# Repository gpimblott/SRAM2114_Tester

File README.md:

# 2114 SRAM Tester

Tester for 2114 SRAM chips using an Arduino Nano. The code can be loaded into the standard Arduino IDE for uploading/editing.

2114 SRAM chips are used in the ZX81, they are 4096 bit chips arranged in 1024 rows of 4 bits.  This code uses a Arduino Nano to perform various tests on a 2114 chip to check that it is working.

The prototype wiring (v01) is outlined in the table below

Port | Arduino  |  2114
-----|----------|--------
PC0  |A0        |IO1
PC1  |A1        |IO2
PC2  |A2        |IO3
PC3  |A3        |IO4
PC4  |A4        |Green LED
PC5  |A5        |Red LED
PC6  |A6        |Switch
PD0  |0         |Serial (Debug) - leave empty for USB
PD1  |1         |Serial (Debug) - leave empty for USB
PD2  |2         |/CS (Chip Select)
PD3  |3         |/WE (Write Enabled)
PD4  |4         |A0
PD5  |5         |A1
PD6  |6         |A2
PD7  |7         |A3
PB0  |8         |A4
PB1  |9         |A5
PB2  |10        |A6
PB3  |11        |A7
PB4  |12        |A8
PB5  |13        |A9

The project is currently is currently at the prototype stage but I am working on a PCB design which should hopefully be available soon.

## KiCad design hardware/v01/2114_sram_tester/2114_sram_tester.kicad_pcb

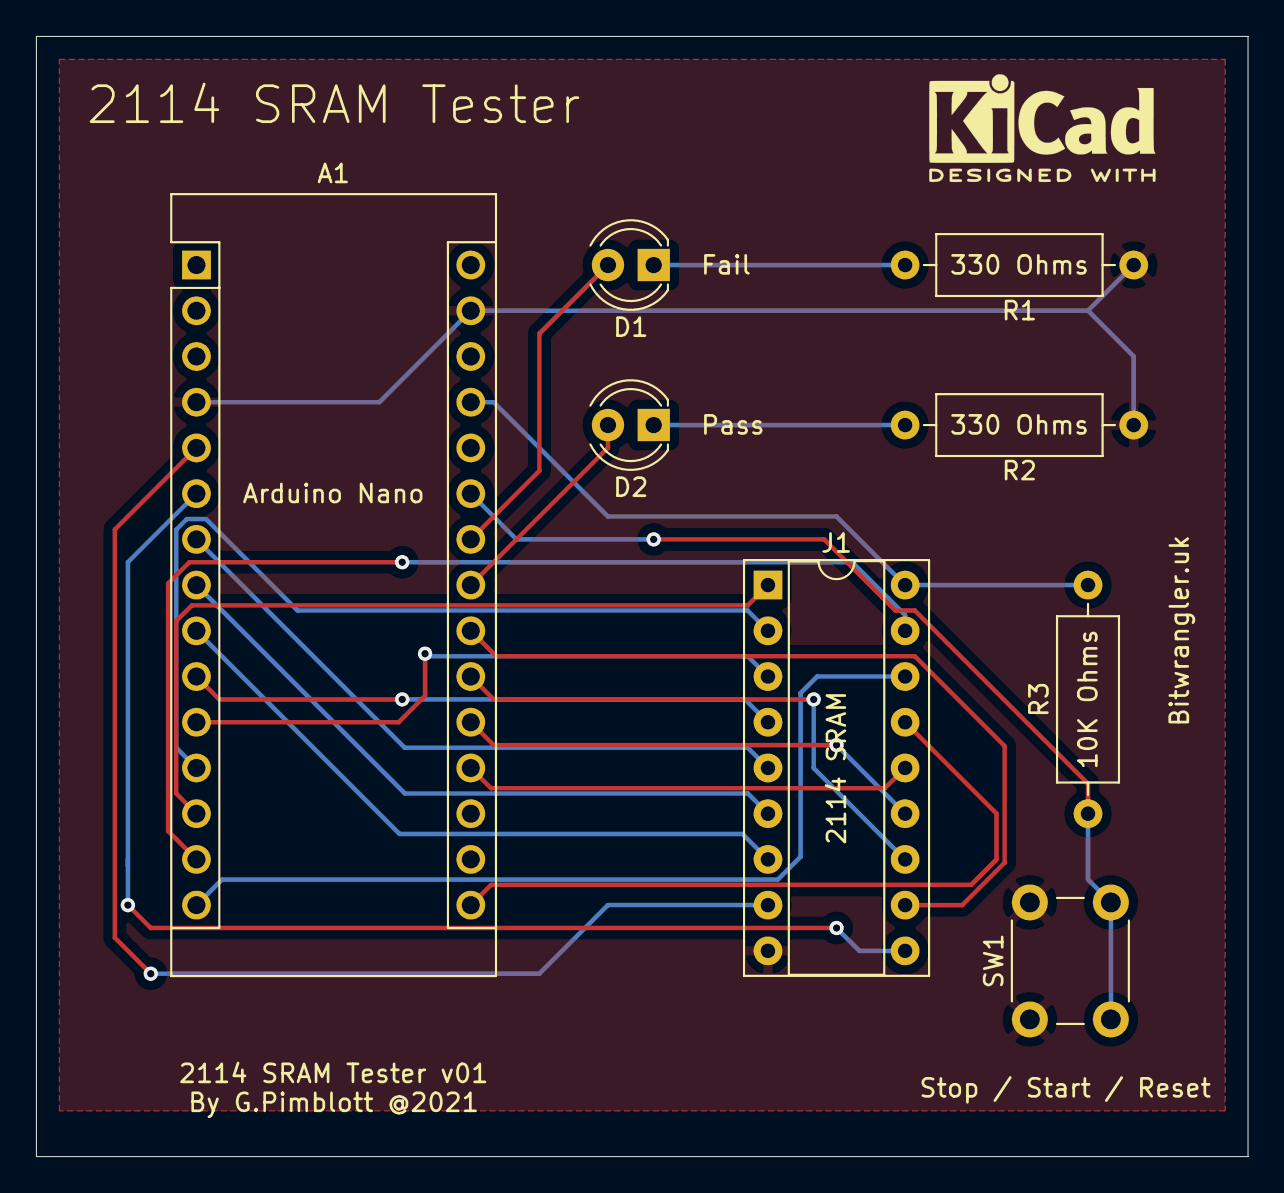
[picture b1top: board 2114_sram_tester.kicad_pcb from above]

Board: 2 copper layers, 67.3 x 62.2 mm, 8 parts (0 on the bottom side), 23 nets.

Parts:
A1: Arduino_Nano_v3.x; Arduino_Nano
D1: RED LED; LED_D4.0mm
D2: GREEN LED; LED_D4.0mm
J1: Conn_02x09_Counter_Clockwise; DIP-18_W7.62mm_Socket
R1, R2: 330Ohms; R_Axial_DIN0309_L9.0mm_D3.2mm_P12.70mm_Horizontal
R3: 10K Ohms; R_Axial_DIN0309_L9.0mm_D3.2mm_P12.70mm_Horizontal
SW1: SW_Push; SW_PUSH_6mm

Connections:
5vPower: A1.27, J1.18, R3.2
Chip_Select: A1.5, J1.8
Data_1: A1.19, J1.14
Data_2: A1.20, J1.13
Data_3: A1.21, J1.12
Data_4: A1.22, J1.11
GND: A1.4, A1.29, J1.9, R1.1, R2.2, SW1.1
Green_LED: A1.23, D2.2
unnamed: D1.1, R1.2
unnamed: D2.1, R2.1
Red_LED: A1.24, D1.2
SRAM_A0: A1.7, J1.5
SRAM_A1: A1.8, J1.6
SRAM_A2: A1.9, J1.7
SRAM_A3: A1.10, J1.4
SRAM_A4: A1.11, J1.3
SRAM_A5: A1.12, J1.2
SRAM_A6: A1.13, J1.1
SRAM_A7: A1.14, J1.17
SRAM_A8: A1.15, J1.16
SRAM_A9: A1.16, J1.15
Switch: A1.25, R3.1, SW1.2
Write_Enable: A1.6, J1.10

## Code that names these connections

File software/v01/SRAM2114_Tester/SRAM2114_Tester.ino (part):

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
   // A6 & A7 can only be analog inputs and don't have internal pulls
   // But that's all I have left to work with
   PC6  A6        Switch

   Special
   -------------------
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#define DATA_PINS 0b00001111    // A0...A3

// LED pins
#define GREEN_LED  0b00010000   // A4
#define RED_LED    0b00100000   // A5

// The serial pins are PD0 and PD1
#define SERIAL_PINS 0b00000011  // D0 & D1
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#define RAM_WE     0b00001000  // Active Low - D3

// Helper Macros for the LEDS
#define green_led_on()  PORTC |= GREEN_LED
#define green_led_off() PORTC &= ~GREEN_LED
#define toggle_green_led() PORTC ^= GREEN_LED

#define red_led_on()    PORTC |= RED_LED
#define red_led_off()   PORTC &= ~RED_LED

// NB: CS and WE are active low so ON==0 and OFF==1
// We don't want to mess with the serial pins on PD0 and PD1 so mask them off
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
#define disable_ram()   PORTD |= (RAM_WE | RAM_CS | SERIAL_PINS)

#define data_in()       DDRC = RED_LED | GREEN_LED;               // LED's output rest input
#define data_out()      DDRC = RED_LED | GREEN_LED | DATA_PINS;   // 0110 1111 - ALL Output except switch

#define SWITCH_PIN  A6

/**
   Global variables
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  DDRB = 0b00111111;       // 0011 1111

  // define switch with internal pullup
  pinMode( SWITCH_PIN, INPUT );

  // Set the initial state of the Chip select and write enabled to OFF
  disable_cs();
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void check_button() {
  boolean pressed = false;

  if ( analogRead(SWITCH_PIN) <= 10 ) {
    pressed = true;
  }

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
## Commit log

2021-07-01 Initial submission
2021-07-04 Add KiCad files
    Initial work on Kicad board design
2021-07-04 Restructure
2021-07-04 Added prototype image
2021-07-04 Resized image
2021-07-04 Resize image
2021-07-06 Added button code
    Button added to stop/start tests
2021-07-06 Updated hardware
    Updated hardware to include stop/start button
2021-07-06 Updated hardware
2021-07-06 Generated Gerber export files and zip
    Generated the necessary files to have a test board made
2021-07-06 Change structure
    Move gerber files to root directory
2021-07-06 Updated code format
2021-07-06 Added board picture
2021-07-06 Added picture to main page
2021-07-06 Added MIT license
2021-07-06 Updated pin definitions to include switch
